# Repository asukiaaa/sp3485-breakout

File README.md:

# sp3485-breakout

## Setup

To install submodules, run the following command after clone.

```
git submodule update --init --recursive
```

## License

MIT

## References

- [Sparkfun Transceiver Breakout](https://www.sparkfun.com/products/10124)
- [Sparkfun Transceiver Breakout schematic (PDF)](https://cdn.sparkfun.com/datasheets/BreakoutBoards/RS485_Breakout_v10.pdf)

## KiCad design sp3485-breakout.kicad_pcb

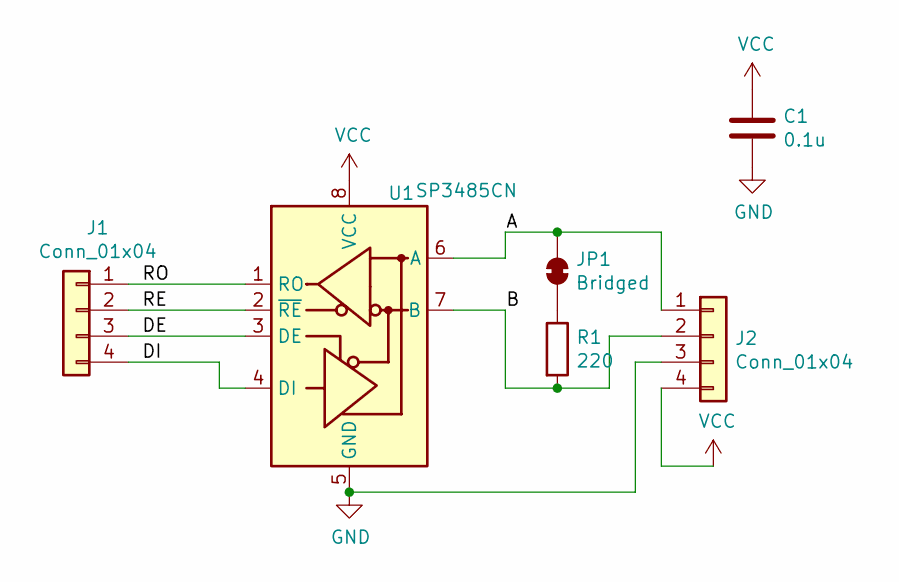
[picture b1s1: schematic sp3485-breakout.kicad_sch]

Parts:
C1: 0.1u; C_0402_1005Metric
J1, J2: Conn_01x04; Pin_1x04_P2.54mm_nosilk
JP1: Bridged; SolderJumper-2_P1.3mm_Bridged_RoundedPad1.0x1.5mm
R1: 220; R_0402_1005Metric
U1: SP3485CN; SOIC-8_3.9x4.9mm_P1.27mm

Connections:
/A: J2.1, JP1.1 (A), U1.6 (A)
/B: J2.2, R1.2, U1.7 (B)
/DE: J1.3, U1.3 (DE)
/DI: J1.4, U1.4 (DI)
/RE: J1.2, U1.2 (~RE)
/RO: J1.1, U1.1 (RO)
GND: C1.2, J2.3, U1.5 (GND)
unnamed: JP1.2 (B), R1.1
VCC: C1.1, J2.4, U1.8 (VCC)

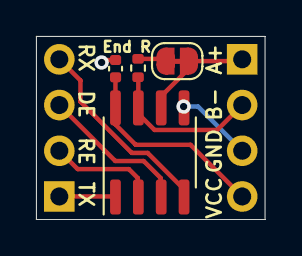
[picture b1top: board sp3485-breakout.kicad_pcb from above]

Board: 2 copper layers, 12.7 x 10.2 mm, 6 parts (0 on the bottom side), 9 nets.

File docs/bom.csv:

Qty,Reference(s),Value,LibPart,Footprint,memo
1,C1,0.1u,Device:C,Capacitor_SMD:C_0402_1005Metric,0.1uf more than 5V 0402inch
2,"J1, J2",Conn_01x04,Connector_Generic:Conn_01x04,my-kicad-footprints:Pin_1x04_P2.54mm_nosilk,
1,R1,220,Device:R,Resistor_SMD:R_0402_1005Metric,1/16W 5% 220Ω 0402inch
1,U1,SP3485CN,Interface_UART:SP3485CN,Package_SO:SOIC-8_3.9x4.9mm_P1.27mm,https://lcsc.com/product-detail/RS-span-style-background-col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

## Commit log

2020-10-31 Update silk and pad position
2020-10-31 Update jumper to mask removed version
2020-11-03 Remove redundant silk and change position of back silk
2020-11-15 Add command to init submodule on readme
2020-11-15 Plot schematic
2020-12-15 Add image to readme
2022-01-12 Add condensor
2022-05-03 Add bom
2024-09-09 Update data for KiCad8
